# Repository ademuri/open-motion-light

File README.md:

# open-motion-light

A battery-powered motion sensor light.

Status: in development (as of July 2025). The current hardware revision, v1.2, mostly works, but has a few small issues. I'm hoping that the next revision will be the "final" version before starting small-scale production for sale.

Ordering and programming one of these units is a relatively complicated project. I don't recommend it unless you're looking for a learning experience, or have completed similar projects before.

## Programming

To easily update the firmware on your unit, and to configure the settings, go to the management page: https://ademuri.github.io/open-motion-light-manager/. This uses the WebSerial browser API, which is only supported in Chromium-based browsers (e.g. Chrome and Edge).

Otherwise, you can build the code yourself using PlatformIO. To build and upload, from the root of this directory run:

```bash
$ pio run -e default -t upload
```

## Firmware

The firmware for this project is written in C++ using the Arduino framework, and built using PlatformIO. It has comprehensive test coverage, which runs on the desktop (also using PlatformIO). You can run the tests with:

```bash
$ pio test -e native
```

### Architecture

Most use of hardware is wrapped in a hardware abstraction layer (HAL) - a thin wrapper class. This allows writing simple fakes for each of these interfaces, for use in tests. This means that the primary control logic is easily testable.

## Fabrication

This board is designed for PCB fabrication and assembly using JLC PCB. The relevant files are in `hardware/production`:

- `open-motion.light.zip` contains the Gerbers, for PCB assembly.
- `bom.csv` is the bill of materials, which contains the list of components.
- `positions.csv` is the positions file - it lists the exact position and orientation of all placed components.

### PCB parameters

Most of JLC's defaults for PCBs are fine. 1.6mm is the best size for this. White soldermask is preferred, since it reflects more light. I highly recommend selecting the 'LeadFree HASL' surface finish - better not to use lead, and it's only a small cost increase.

### Assembly parameters

This design requires PCBA Type 'Standard', since it needs assembly on both sides. Most of the components are on the top, except the USB port, battery holder, power switch, and reset button. For small quantities, this adds moderate cost, but the USB port would be difficult (although not impossible) to solder by hand. The rest of the parameters can be left as default.

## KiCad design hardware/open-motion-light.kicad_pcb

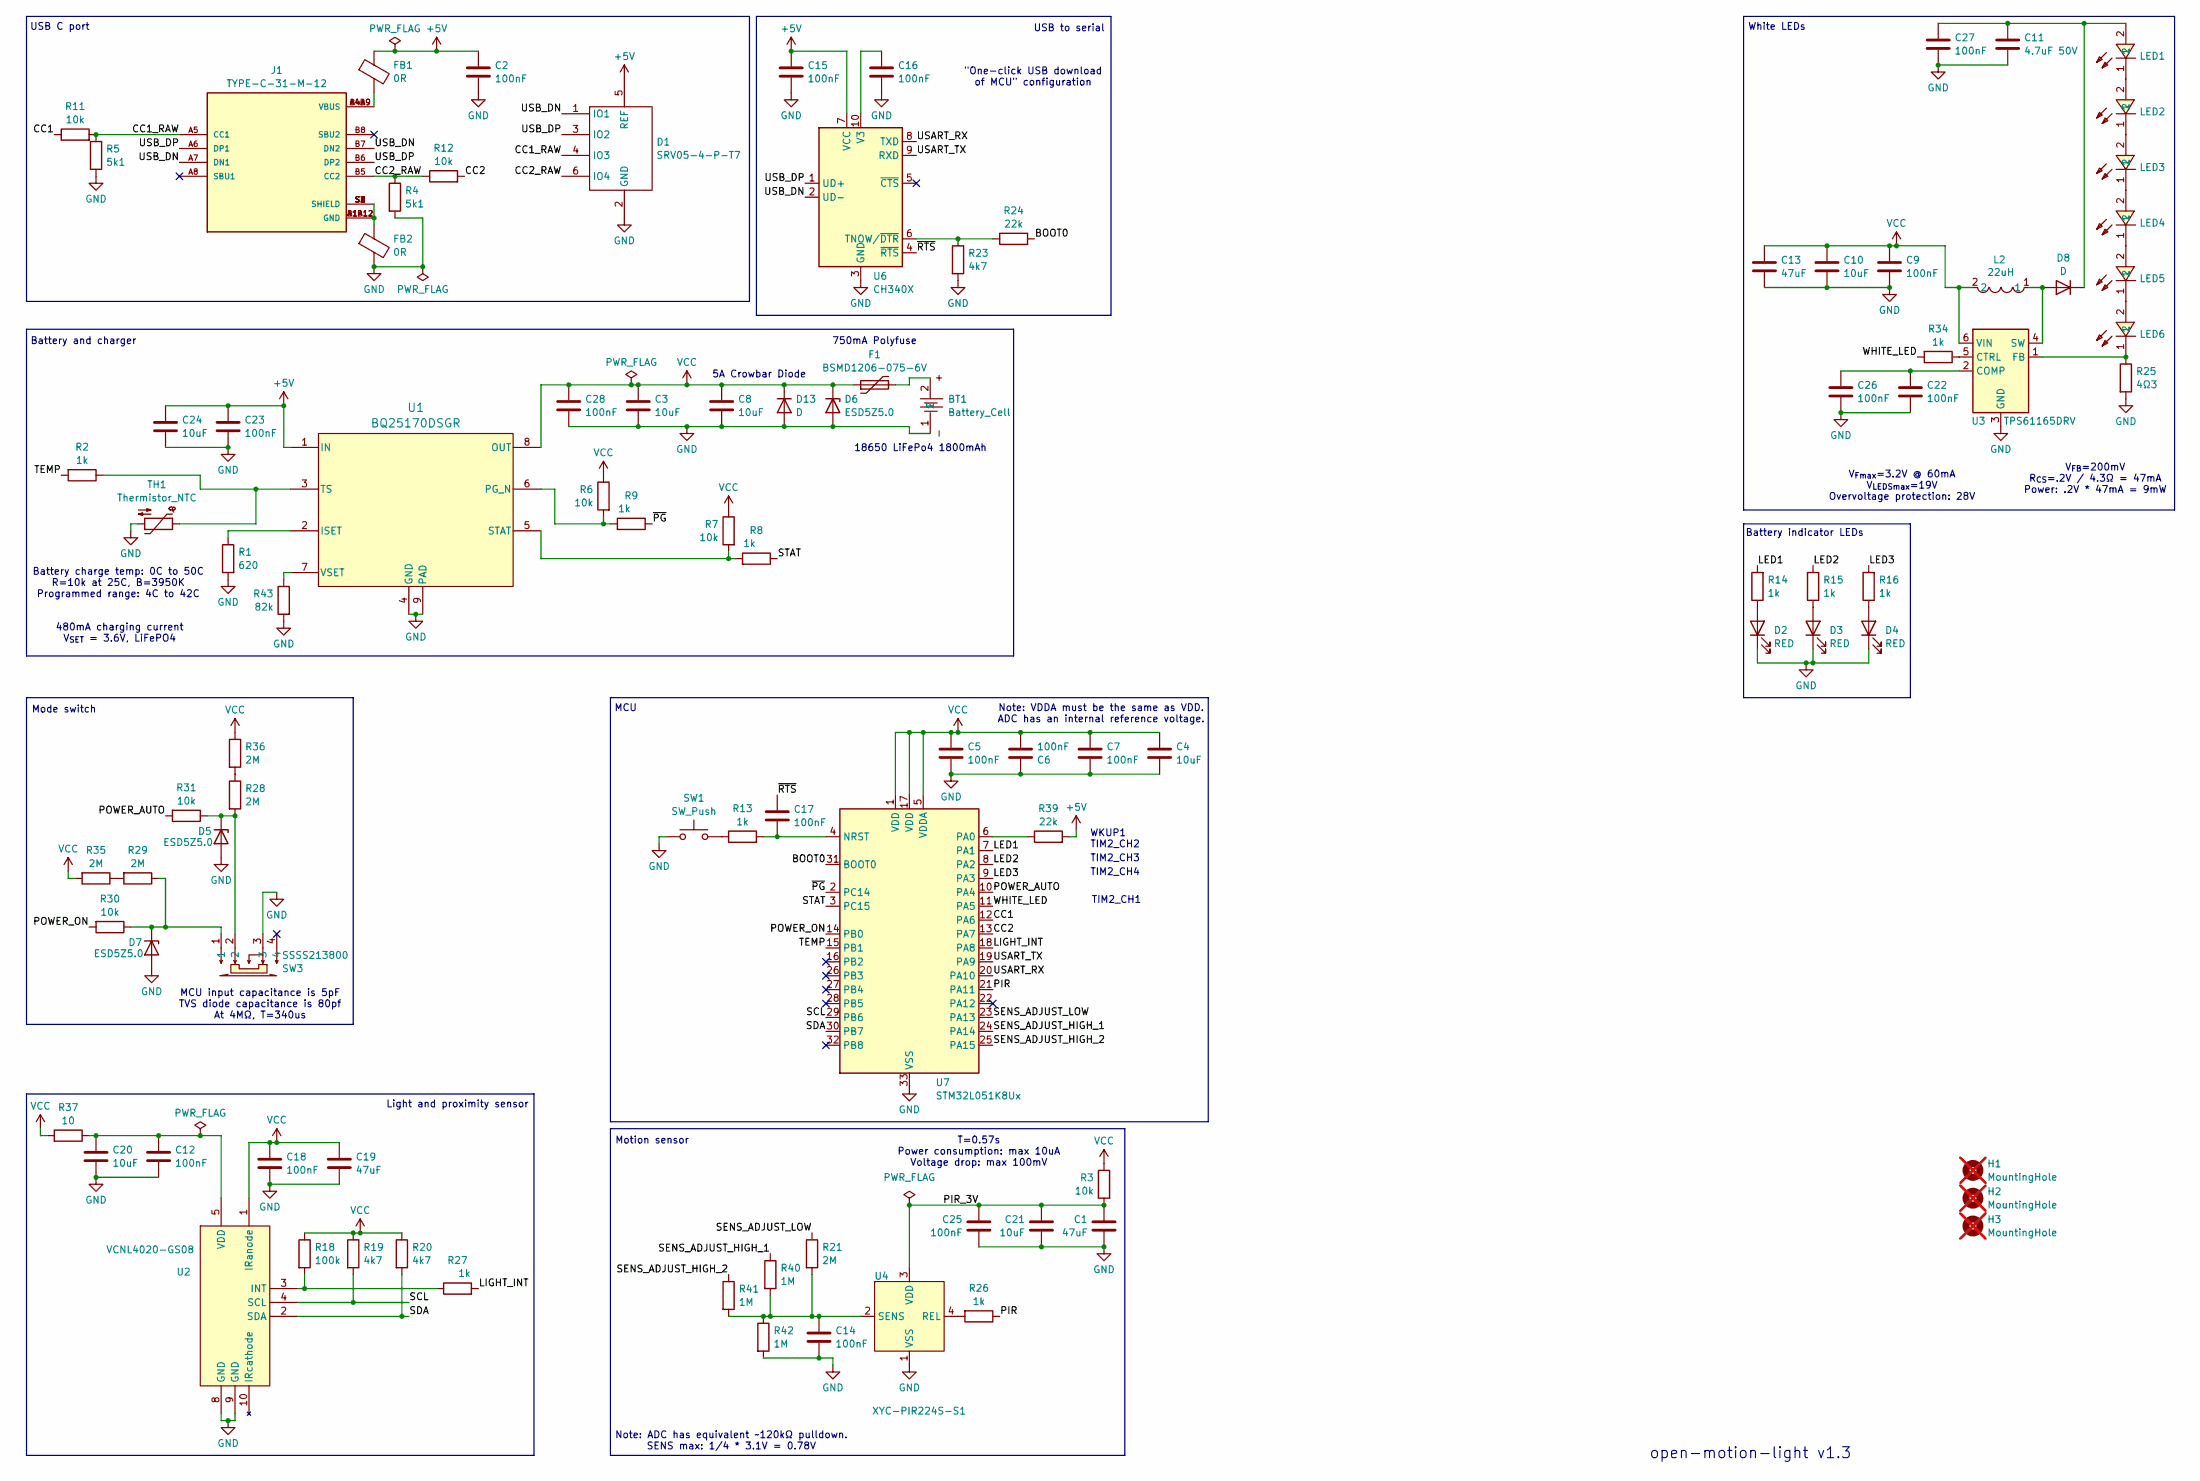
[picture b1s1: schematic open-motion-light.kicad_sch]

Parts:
BT1: Battery_Cell; BAT-TH_BH-18650-A1AJ005; LCSC Part C5290176
C1, C13, C19: 47uF; C_1206_3216Metric; LCSC C96123
C2, C5, C6, C7, C9, C12, C14, C15, C16, C17, C18, C22, C23, C25, C26, C27, C28: 100nF; C_0402_1005Metric; LCSC C307331
C3, C4, C8, C10, C20, C21, C24: 10uF; C_0603_1608Metric; LCSC C96446
C11: 4.7uF 50V; C_1206_3216Metric; LCSC C51205
D1: SRV05-4-P-T7; SOT-23-6; LCSC C85364
D2, D3, D4: RED; LED_0603_1608Metric; LCSC C2286
D5, D6, D7: ESD5Z5.0; D_SOD-523; LCSC C5199848
D8, D13: D; D_SMA; LCSC C22452
F1: BSMD1206-075-6V; Fuse_1206_3216Metric; LCSC C883127
FB1, FB2: 0R; L_1206_3216Metric; LCSC C17888
H1, H2, H3: MountingHole; MountingHole_3.2mm_M3_ISO7380; not fitted
J1: TYPE-C-31-M-12; HRO_TYPE-C-31-M-12; PARTREV A; LCSC C165948
L2: 22uH; L_Sunlord_SWPA4030S; LCSC Part C83472
LED1, LED2, LED3, LED4, LED5, LED6: HL-AM-2835H421W-S1-08-HR3; LED-SMD_L3.3-W2.8-RD; LCSC Part C210315
R1: 620; R_0603_1608Metric_Pad0.98x0.95mm_HandSolder; LCSC C23220
R2, R8, R9, R13, R14, R15, R16, R26, R27, R34: 1k; R_0402_1005Metric; LCSC C11702
R3, R6, R7, R11, R12, R30, R31: 10k; R_0402_1005Metric; LCSC C25744
R4, R5: 5k1; R_0402_1005Metric; LCSC C25905
R18: 100k; R_0402_1005Metric; LCSC C25741
R19, R20, R23: 4k7; R_0402_1005Metric; LCSC C25900
R21, R28, R29, R35, R36: 2M; R_0603_1608Metric; LCSC C22976
R24, R39: 22k; R_0402_1005Metric; LCSC C25768
R25: 4Ω3; R_0603_1608Metric; LCSC C2933230
R37: 10; R_0402_1005Metric; LCSC C25077
R40, R41, R42: 1M; R_0603_1608Metric; LCSC C22935
R43: 82k; R_0402_1005Metric; LCSC C2909388
SW1: SW_Push; SW_TACTILE_5.1MM_TS-1187A-C-D-B; LCSC C318884
SW3: SSSS213800; SW-SMD_SSSS213800; LCSC Part C361168
TH1: Thermistor_NTC; R_0603_1608Metric; LCSC C279936
U1: BQ25170DSGR; Texas_DSG0008A_WSON-8-1EP_2x2mm_P0.5mm_EP0.9x1.6mm_ThermalV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; LCSC C5208201
U2: VCNL4020-GS08; SENSOR-SMD_VCNL4020-GS08; LCSC Part C511034
U3: TPS61165DRV; WSON-6-1EP_2x2mm_P0.65mm_EP1x1.6mm_ThermalVias; LCSC C122568
U4: XYC-PIR224S-S1; TO-5-4_BD9.2-P2.54_XYC-PIR224D-D0; LCSC Part C6081347
U6: CH340X; MSOP-10_3x3mm_P0.5mm; LCSC C3035748
U7: STM32L051K8Ux; QFN-32-1EP_5x5mm_P0.5mm_EP3.45x3.45mm; LCSC C516778

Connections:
+5V: C2.1, C15.1, C23.2, C24.1, D1.5 (REF), FB1.1, R39.2, U1.1 (IN), U6.7 (VCC)
/BOOT0: R24.2, U7.31 (BOOT0)
/CC1: R11.1, U7.12 (PA6)
/CC1_RAW: D1.4 (IO3), J1.A5 (CC1), R5.1, R11.2
/CC2: R12.2, U7.13 (PA7)
/CC2_RAW: D1.6 (IO4), J1.B5 (CC2), R4.1, R12.1
/LED1: R14.2, U7.7 (PA1)
/LED2: R15.2, U7.8 (PA2)
/LED3: R16.2, U7.9 (PA3)
/LIGHT_INT: R27.2, U7.18 (PA8)
/PIR: R26.1, U7.21 (PA11)
/PIR_3V: C1.2, C21.1, C25.1, R3.2, U4.3 (VDD)
/POWER_AUTO: R31.2, U7.10 (PA4)
/POWER_ON: R30.2, U7.14 (PB0)
/SCL: R19.2, U2.4 (SCL), U7.29 (PB6)
/SDA: R20.2, U2.2 (SDA), U7.30 (PB7)
/SENS_ADJUST_HIGH_1: R40.1, U7.24 (PA14)
/SENS_ADJUST_HIGH_2: R41.1, U7.25 (PA15)
/SENS_ADJUST_LOW: R21.1, U7.23 (PA13)
/STAT: R8.1, U7.3 (PC15)
/TEMP: R2.2, U7.15 (PB1)
/USART_RX: U6.8 (TXD), U7.20 (PA10)
/USART_TX: U6.9 (RXD), U7.19 (PA9)
/USB_DN: D1.1 (IO1), J1.A7 (DN1), J1.B7 (DN2), U6.2 (UD-)
/USB_DP: D1.3 (IO2), J1.A6 (DP1), J1.B6 (DP2), U6.1 (UD+)
/WHITE_LED: R34.2, U7.11 (PA5)
/~PG: R9.1, U7.2 (PC14)
/~RTS: C17.1, U6.4 (~RTS)
GND: BT1.1, C1.1, C2.2, C3.2, C4.2, C5.2, C6.1, C7.2, C8.2, C9.2, C10.2, C11.2, C12.1, C13.1, C14.2, C15.2, C16.2, C18.1, C19.1, C20.2, C21.2, C22.2, C23.1, C24.2, C25.2, C26.2, C27.2, C28.1, D1.2 (GND), D2.1 (K), D3.1 (K), D4.1 (K), D5.2 (A), D6.2 (A), D7.2 (A), D13.2 (A), FB2.2, R1.2, R4.2, R5.2, R23.2, R25.2, R42.2, R43.2, SW1.1, SW3.3, TH1.2, U1.4 (GND), U1.9 (PAD), U2.8 (GND), U2.9 (GND), U3.3 (GND), U3.7 (GND), U4.1 (VSS), U6.3 (GND), U7.33 (VSS)
unnamed: BT1.2, F1.2
unnamed: D2.2 (A), R14.1
unnamed: D3.2 (A), R15.1
unnamed: D4.2 (A), R16.1
unnamed: D5.1 (K), R28.2, R31.1, SW3.2
unnamed: D7.1 (K), R29.1, R30.1, SW3.1
unnamed: D8.2 (A), L2.1, U3.4 (SW)
unnamed: C11.1, C27.1, D8.1 (K), LED1.2
unnamed: FB1.2, J1.A4B9 (VBUS), J1.B4A9 (VBUS)
unnamed: FB2.1, J1.A1B12 (GND), J1.B1A12 (GND), J1.S1 (SHIELD), J1.S2 (SHIELD), J1.S3 (SHIELD), J1.S4 (SHIELD)
unnamed: LED1.1, LED2.2
unnamed: LED2.1, LED3.2
unnamed: LED3.1, LED4.2
unnamed: LED4.1, LED5.2
unnamed: LED5.1, LED6.2
unnamed: R13.1, SW1.2
unnamed: R28.1, R36.2
unnamed: R29.2, R35.1
unnamed: R1.1, U1.2 (ISET)
unnamed: R6.2, R9.2, U1.6 (PG_N)
unnamed: R7.2, R8.2, U1.5 (STAT)
unnamed: R2.1, TH1.1, U1.3 (TS)
unnamed: R43.1, U1.7 (VSET)
unnamed: R18.2, R27.1, U2.3 (INT)
unnamed: C12.2, C20.1, R37.1, U2.5 (VDD)
unnamed: C22.1, C26.1, U3.2 (COMP)
unnamed: R34.1, U3.5 (CTRL)
unnamed: LED6.1, R25.1, U3.1 (FB)
unnamed: R26.2, U4.4 (REL)
unnamed: C14.1, R21.2, R40.2, R41.2, R42.1, U4.2 (SENS)
unnamed: R23.1, R24.1, U6.6 (TNOW/~DTR)
unnamed: C16.1, U6.10 (V3)
unnamed: C17.2, R13.2, U7.4 (NRST)
unnamed: R39.1, U7.6 (PA0)
VCC: C3.1, C4.1, C5.1, C6.2, C7.1, C8.1, C9.1, C10.1, C13.2, C18.2, C19.2, C28.2, D6.1 (K), D13.1 (K), F1.1, L2.2, R3.1, R6.1, R7.1, R18.1, R19.1, R20.1, R35.2, R36.1, R37.2, U1.8 (OUT), U2.1 (IRanode), U3.6 (VIN), U7.1 (VDD), U7.5 (VDDA), U7.17 (VDD)

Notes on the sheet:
TIM2_CH1
V_{FB}=200mV R_{CS}=.2V / 4.3Ω = 47mA Power: .2V * 47mA = 9mW
Battery and charger
V_{Fmax}=3.2V @ 60mA V_{LEDSmax}=19V Overvoltage protection: 28V
White LEDs
"One-click USB download of MCU" configuration
USB C port
T=0.57s Power consumption: max 10uA Voltage drop: max 100mV
TIM2_CH2
Light and proximity sensor
TIM2_CH4
Battery charge temp: 0C to 50C R=10k at 25C, B=3950K Programmed range: 4C to 42C
480mA charging current V_{SET} = 3.6V, LiFePO4
open-motion-light v1.3
5A Crowbar Diode
18650 LiFePo4 1800mAh
WKUP1
TIM2_CH3
750mA Polyfuse
Mode switch
USB to serial
Note: ADC has equivalent ~120kΩ pulldown. SENS max: 1/4 * 3.1V = 0.78V
Note: VDDA must be the same as VDD. ADC has an internal reference voltage.
Battery indicator LEDs
MCU
Motion sensor
MCU input capacitance is 5pF TVS diode capacitance is 80pf At 4MΩ, T=340us

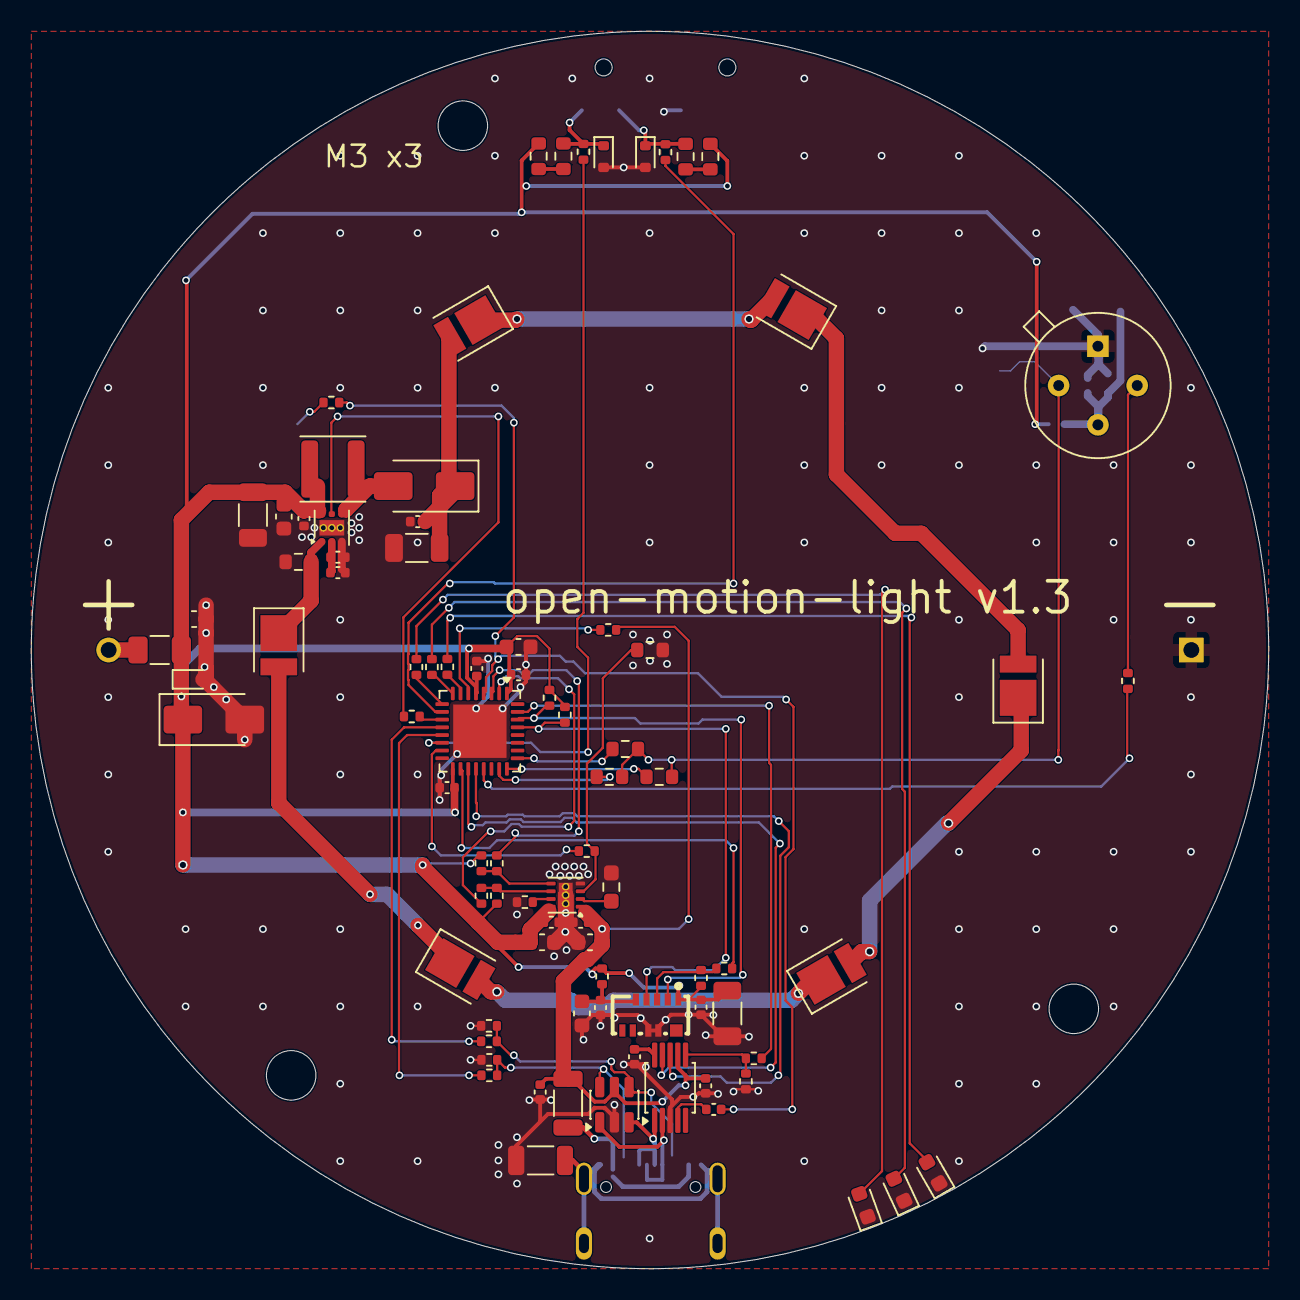
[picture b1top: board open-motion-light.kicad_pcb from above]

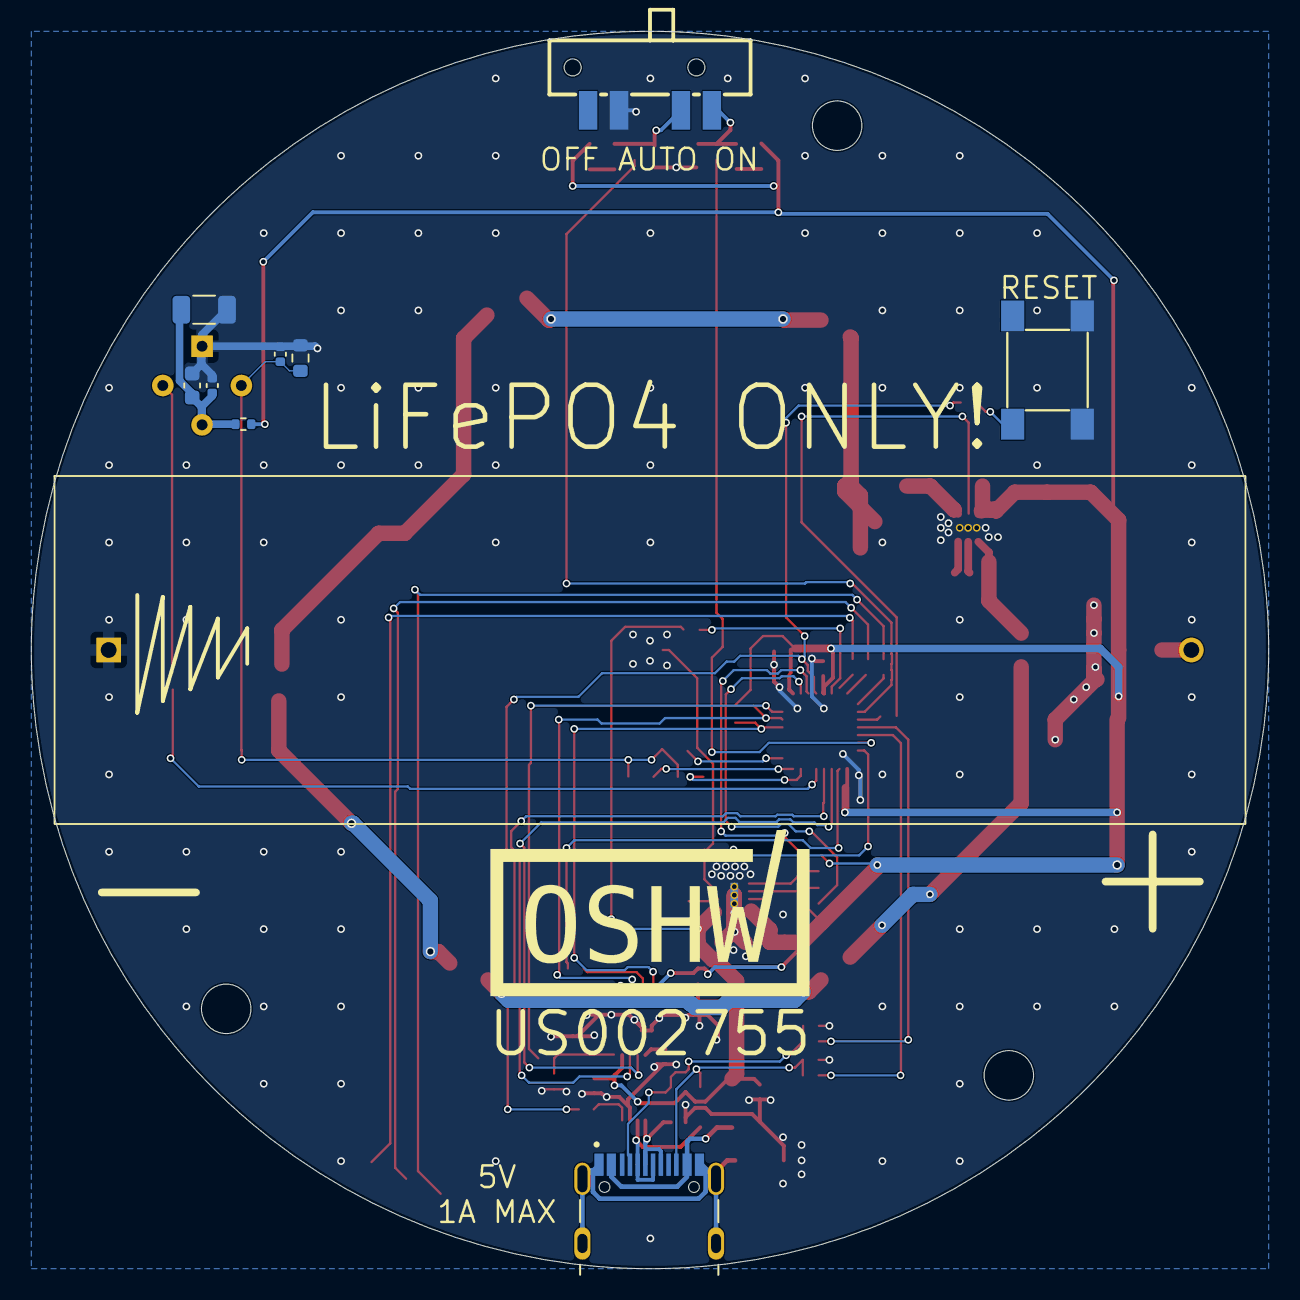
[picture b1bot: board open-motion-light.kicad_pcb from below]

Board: 4 copper layers, 80.0 x 80.0 mm, 98 parts (10 on the bottom side), 64 nets.

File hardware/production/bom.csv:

Designator,Footprint,Quantity,Value,LCSC Part #
BT1,BAT-TH_BH-18650-A1AJ005,1,Battery_Cell,C5290176
"C1, C13, C19",1206,3,47uF,C96123
"C10, C20, C21, C24, C3, C4, C8",0603,7,10uF,C96446
C11,1206,1,4.7uF 50V,C51205
"C12, C14, C15, C16, C17, C18, C2, C22, C23, C25, C26, C27, C28, C5, C6, C7, C9",0402,17,100nF,C307331
D1,SOT-23-6,1,SRV05-4-P-T7,C85364
"D13, D8",D_SMA,2,D,C22452
"D2, D3, D4",0603,3,RED,C2286
"D5, D6, D7",D_SOD-523,3,ESD5Z5.0,C5199848
F1,1206,1,BSMD1206-075-6V,C883127
"FB1, FB2",1206,2,0R,C17888
J1,HRO_TYPE-C-31-M-12,1,TYPE-C-31-M-12,C165948
L2,L_Sunlord_SWPA4030S,1,22uH,C83472
"LED1, LED2, LED3, LED4, LED5, LED6",LED-SMD_L3.3-W2.8-RD,6,HL-AM-2835H421W-S1-08-HR3,C210315
R1,0603,1,620,C23220
"R11, R12, R3, R30, R31, R6, R7",0402,7,10k,C25744
"R13, R14, R15, R16, R2, R26, R27, R34, R8, R9",0402,10,1k,C11702
R18,0402,1,100k,C25741
"R19, R20, R23",0402,3,4k7,C25900
"R21, R28, R29, R35, R36",0603,5,2M,C22976
"R24, R39",0402,2,22k,C25768
R25,0603,1,4Ω3,C2933230
R37,0402,1,10,C25077
"R4, R5",0402,2,5k1,C25905
"R40, R41, R42",0603,3,1M,C22935
R43,0402,1,82k,C2909388
SW1,SW_TACTILE_5.1MM_TS-1187A-C-D-B,1,SW_Push,C318884
SW3,SW-SMD_SSSS213800,1,SSSS213800,C361168
TH1,0603,1,Thermistor_NTC,C279936
U1,Texas_DSG0008A_WSON-8-1EP_2x2mm_P0.5mm_EP0.9x1.6mm_ThermalVias,1,BQ25170DSGR,C5208201
U2,SENSOR-SMD_VCNL4020-GS08,1,VCNL4020-GS08,C511034
U3,WSON-6-1EP_2x2mm_P0.65mm_EP1x1.6mm_ThermalVias,1,TPS61165DRV,C122568
U4,TO-5-4_BD9.2-P2.54_XYC-PIR224D-D0,1,XYC-PIR224S-S1,C6081347
U6,MSOP-10_3x3mm_P0.5mm,1,CH340X,C3035748
U7,QFN-32-1EP_5x5mm_P0.5mm_EP3.45x3.45mm,1,STM32L051K8Ux,C516778

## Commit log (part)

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2024-04-07 Start schematic - add USB port and charge controller
2024-04-07 Add input protection to USB and charger
2024-04-07 Add LEDs and uC
2024-04-08 Add battery protection
2024-04-11 Add hardware/.gitignore
2024-04-11 Start adding MT9284 LED driver
2024-04-12 Finish LED driver. Add motion sensor and PIR.
2024-04-12 Update processor to STM32L031G6Ux. Add CH340x. Organize some blocks.
2024-04-14 First draft of schematic completed
2024-04-14 Assign LCSC part numbers and footprints
2024-04-20 Migrate three resistors to basic components, continue placement
2024-04-28 Continue placement
2024-04-29 Finish placement
2024-04-29 First pass at routing
2024-04-29 Add lots of stitching vias
2024-04-29 Hardware revision v1.0
2024-04-30 Add empty PIO project with board definition
2024-04-30 Add pin definitions and mode setting
2024-05-03 Start adding controller: add power mode management
2024-05-03 Add white LED motion control
2024-05-03 Update main
2024-05-03 Read the battery voltage
2024-05-03 Test battery filtering
2024-05-03 Cleanup: rename battery functions and remove uneeded variable
2024-05-04 Add library for VCNL4010 ambient light and proximity sensor
2024-05-04 Add an option to debug the VCNL4010
2024-05-04 Move PowerMode out of Controller
2024-05-04 Add logic for PowerStatus
2024-05-04 Cleanup Controller class definition
2024-05-04 Add USB status enum
2024-05-04 Add test coverage for setting charge current
2024-05-04 Add handling for charger error
2024-05-04 Display battery voltage level
2024-05-05 Upgrade compiler feature version to C++17
2024-05-05 Dimly light up inactive battery indicator LEDs
2024-05-05 Add TODO for blocking VCNL4010 calls
2024-05-06 Use #define control for serial debugging
2024-05-06 Configure the processor to run at 1MHz
2024-05-06 Set F_CPU flag
2024-05-07 Stop some timers
2024-05-07 Fix upload command and comment out CPU speed flags
2024-05-07 Testing updates: reduce PWM frequency and tune some values
2024-05-07 Fix serial monitor config
2024-05-07 Fix serial output
2024-05-07 Add define-control for custom clock
2024-05-07 Fix controller test for battery LED workaround
2024-05-07 Add test coverage that ALS+Prox sensor is initialized
2024-05-13 WIP start designing enclosure for v1.0
2024-05-14 Add cutouts to enclosure bottom
2024-05-15 Add switch boot and snap fit pockets
2024-05-15 Start fixing topological naming issues
2024-05-15 Complete TNP updates
2024-05-16 First pass at cover
2024-05-17 More v1.1 schematic updates
2024-05-20 Add short description to the readme
2024-05-20 Add contributing doc
2024-05-20 Add Apache 2.0 license headers
2024-05-20 Add license file
2024-05-21 Start updating placement and routing for v1.1
2024-05-26 Re-organize schematic
2024-05-27 Update PCB for circle layout
2024-05-29 Place and route LEDs, driver, and USB power
2024-05-30 Hardware revision v1.1
2024-06-07 Move clock to custom-clock to avoid conflict with platform lib
2024-06-07 Add JLC part number for light sensor
2024-06-07 Migrate software to STM32L051K8U for hardware v1.1
2024-06-07 Add note about updating local version of Arduino
2024-06-07 Use analogWrite for all battery LEDs, and init 5v detect pin
2024-06-07 Migrate software to VCNL4020 for v1.1
2024-06-07 Handle startup failure
2024-06-07 Increase LED PWM frequency
2024-06-12 Statically set the I2C timing
2024-06-12 Migrate to Serial1 for v1.1
2024-06-12 Remove unneeded defines
2024-06-12 Add documentation on setting the i2c timing
2024-06-13 Fix test for VCNL v1.1 change
2024-06-13 Ignore motion sensor right after changing the main LED
2024-06-13 Go to stop mode when the LED is off
2024-06-13 Fix sleep logic
2024-06-16 Add measurements for LED current draw
2024-06-16 Fix sleep wakeup time correction
2024-06-16 Add low battery cutoff logic
2024-06-16 Don't turn on the main LED when charging but below cutoff
2024-06-16 Add sleep lockout timer
2024-06-16 Prevent white LED flash on startup
2024-06-16 Fix LTO warning
2024-06-16 Set I2C timing value for SM mode
2024-06-16 Add hysteresis to battery low logic
2024-06-19 Fix board definition hack in readme
2024-06-24 Gate LED on ambient brightness
2024-08-30 Increase sleep lockout timer.
    This fixes a bug where the LED sometimes does not turn on when switching
    from on to auto.
2024-09-05 Start updating schematic for v1.2
2024-10-26 Remove build note from readme, no longer needed
2024-10-26 Update arduino-timer version: handle millis rollover
2024-10-26 Add test coverage for millis rollover
2024-10-26 Fix sleep mode power consumption
2024-12-25 Fast blink status LEDs on charge error
2024-12-31 Tentative hardware v1.2
2025-01-03 v1.2: remove PIR pulldown
2025-01-30 Hardware v1.2
2025-02-01 Fix showing battery status immediately on plugging in
2025-02-01 Initialize STM32RTC
2025-02-03 Update STM32LowPower and STM32RTC versions
2025-02-03 Update USB-C port 3D model
2025-02-03 Add param to disable battery LEDs
2025-02-03 Add brightness modes
2025-02-03 Add a config object
2025-02-03 Fix compiler warning
2025-02-03 Add auto brightness threshold to config
2025-02-04 Ignore brightness while LED is on
2025-02-04 Implement VCNL4020 proximity detection
2025-02-05 Add proximity debugging print code
2025-02-05 Start implementing proximity toggle
2025-02-11 Trigger battery display when turning off
2025-02-11 Use a constant for battery led brightness
2025-02-12 Default prox off
2025-02-12 Don't sleep while battery LEDs are active
2025-02-12 WIP go into stop mode when the battery is low
2025-02-14 Document low-power mode consumption
2025-03-02 Add serial-send.sh
2025-04-01 Don't turn on main LEDs while charging
2025-04-01 Enable prox sensor when ON and set current to max
2025-04-01 Add serial spam option
2025-04-01 Force high charging
2025-04-02 git subrepo clone git@github.com:ademuri/open-motion-light-protos.git proto
    subrepo:
    subdir: "proto"
    merged: "b1ec104"
    upstream:
    origin: "git@github.com:ademuri/open-motion-light-protos.git"
    branch: "main"
2025-04-03 Add serial port interface and implementation
2025-04-03 Add basic proto with serial encode/decode
2025-04-03 Add lint script
2025-04-03 Add CI to build and test with PIO
2025-04-03 Split build and test in CI
2025-04-03 Add lint and fix PIO test CI config
2025-04-03 Fix style for linter check
2025-04-03 Fix path problem in test CI
2025-04-03 Cache Python in test CI
2025-04-03 Use a fixed path for Python in test CI
2025-04-03 Test CI: cache python to ~/.local
2025-04-03 Test CI: re-try at caching PIO
2025-04-03 Test CI: bump setup-python version to v5
2025-04-03 Test CI: install PIO packages in setup for caching
2025-04-03 Test CI: include package versions in cache hash
2025-04-03 Fully specify nanopb deps
2025-04-03 Test CI: empty platformio change
2025-04-03 Test CI: include .pio in cache
2025-04-03 Test CI: build twice
2025-04-03 git subrepo push proto
    subrepo:
    subdir: "proto"
    merged: "9f5b4a7"
    upstream:
    origin: "git@github.com:ademuri/open-motion-light-protos.git"
    branch: "main"
2025-04-05 Change battery voltage to be millivolts/int in the proto
2025-04-05 git subrepo pull proto
    subrepo:
    subdir: "proto"
    merged: "9a2429e"
    upstream:
    origin: "git@github.com:ademuri/open-motion-light-protos.git"
    branch: "main"
2025-04-05 git subrepo push proto
    subrepo:
    subdir: "proto"
    merged: "5dfda1b"
    upstream:
    origin: "git@github.com:ademuri/open-motion-light-protos.git"
    branch: "main"
2025-04-05 git subrepo push proto
    subrepo:
    subdir: "proto"
    merged: "1bde24f"
    upstream:
    origin: "git@github.com:ademuri/open-motion-light-protos.git"
    branch: "main"
2025-04-05 Add firmware version via build stamping
2025-04-05 Switch to using a proto for config
2025-04-05 Include the current config in the serial response
2025-04-05 git subrepo push proto
    subrepo:
    subdir: "proto"
    merged: "04f540d"
    upstream:
    origin: "git@github.com:ademuri/open-motion-light-protos.git"
    branch: "main"
2025-04-05 Allow setting config in RAM
2025-04-05 Re-organize proto layout
2025-04-05 git subrepo push proto
    subrepo:
    subdir: "proto"
    merged: "630343b"
    upstream:
    origin: "git@github.com:ademuri/open-motion-light-protos.git"
    branch: "main"
2025-04-05 Fix tests
2025-04-08 Fix arduino build; actually save config
2025-04-10 Fix build error in fake-eeprom.h
2025-04-10 Add tests for SerialManager
2025-04-10 Move timeout and duty cycle to the config proto
2025-04-10 Move remaining config value into the proto
2025-04-11 Format
2025-04-11 git subrepo push proto
    subrepo:
    subdir: "proto"
    merged: "0fa5035"
    upstream:
    origin: "git@github.com:ademuri/open-motion-light-protos.git"
    branch: "main"
2025-04-11 Add note about keeping config defaults in sync with UI
2025-04-11 Add action to package firmware
2025-04-11 Don't build firmware on every push to main
2025-04-11 Tag push: create release instead of artifact
2025-04-11 Tag push: add write permission
2025-04-16 Add prox and ALS sensor readings to status proto
2025-04-16 git subrepo push proto
    subrepo:
    subdir: "proto"
    merged: "4f45ff2"
    upstream:
    origin: "git@github.com:ademuri/open-motion-light-protos.git"
    branch: "main"
2025-04-17 Enable sensors when USB is plugged in
2025-05-17 Fix serial manager test
2025-05-17 Add basic ramper library
2025-05-17 Update ramper to have separate up and down limits
2025-05-17 Add light ramp up and down time
2025-05-17 Ramp the LED up and down
2025-05-17 Fix LED ramp to use periods > duty cycles
2025-05-17 Re-set ramper when config is updated
2025-06-18 Remove unused todo from platformio.ini
2025-07-04 Add documentation to the README
2025-07-04 Add status to readme
2025-08-28 Hardware v1.3 first pass
2025-09-09 Document some decisions for hardware v1.3
2025-09-09 WIP start updating for sourcing
2025-09-09 Convert to KiCAD v9
2025-09-09 Schematic updates for v1.3 (again)
2025-09-26 git subrepo push proto
    subrepo:
    subdir: "proto"
    merged: "e6dc9c5"
    upstream:
    origin: "git@github.com:ademuri/open-motion-light-protos.git"
    branch: "main"
2025-09-26 Fix typo in comment
2025-09-26 Fix hardware version proto definition
2025-09-26 git subrepo push proto
    subrepo:
    subdir: "proto"
    merged: "805ac56"
    upstream:
    origin: "git@github.com:ademuri/open-motion-light-protos.git"
    branch: "main"
2025-09-26 Add hardware version to ConfigPb
2025-09-26 Add note on thermal performance of battery charger IC
2025-09-26 Re-add optional to SerialRequest and SerialResponse.
    These are needed for nanopb to generate `has_foo` functions.
2025-09-26 Fix proto subrepo parent
2025-09-26 git subrepo push proto
    subrepo:
    subdir: "proto"
    merged: "8450f55"
    upstream:
    origin: "git@github.com:ademuri/open-motion-light-protos.git"
    branch: "main"
2025-10-04 Add motion sensitivity to the proto
2025-10-04 Add tests for setting sensitivity pins
2025-10-04 git subrepo pull proto
    subrepo:
    subdir: "proto"
    merged: "9cc9d99"
    upstream:
    origin: "git@github.com:ademuri/open-motion-light-protos.git"
    branch: "main"
2025-10-04 git subrepo push proto
    subrepo:
    subdir: "proto"
    merged: "70b991f"
    upstream:
    origin: "git@github.com:ademuri/open-motion-light-protos.git"
    branch: "main"
2025-10-04 Update motion sensitivity to use HIGH or INPUT_ANALOG
2025-10-04 Update fake pin config values to match STM32
2025-10-04 Add scaffolding for temperature sensor
2025-10-04 Add temperature to StatusPb
2025-10-04 Set the temperature in serial response
2025-10-04 git subrepo push proto
    subrepo:
    subdir: "proto"
    merged: "849e290"
    upstream:
    origin: "git@github.com:ademuri/open-motion-light-protos.git"
    branch: "main"
2026-02-16 Add AGENTS.md
2026-02-16 Initialize SerialManager.
    This fixes the tests.
2026-02-16 Don't sleep for the first second of turning on.
    This fixes an issue in the firmware where the device wouldn't respond on
    the serial port for about a minute after plugging it in.
2026-02-16 Don't sleep when USB connected or 5V detected
2026-02-17 Call ConfigUpdated in Controller::Init()
2026-02-17 Check pin modes in the tests
2026-02-17 Move pinMode calls to Controller::Init()
2026-02-18 Remove old config todo
2026-02-18 Remove unused serial todo
